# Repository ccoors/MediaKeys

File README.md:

# MediaKeys

| 1  | 2 |
| ------------- | ------------- |
| Play/Pause | Stop  |
| Previous | Next |
| Volume - | Volume + |

The Arduino sketch requires the [Arduino HID Project](https://github.com/NicoHood/HID) (installable from the Arduino IDE)

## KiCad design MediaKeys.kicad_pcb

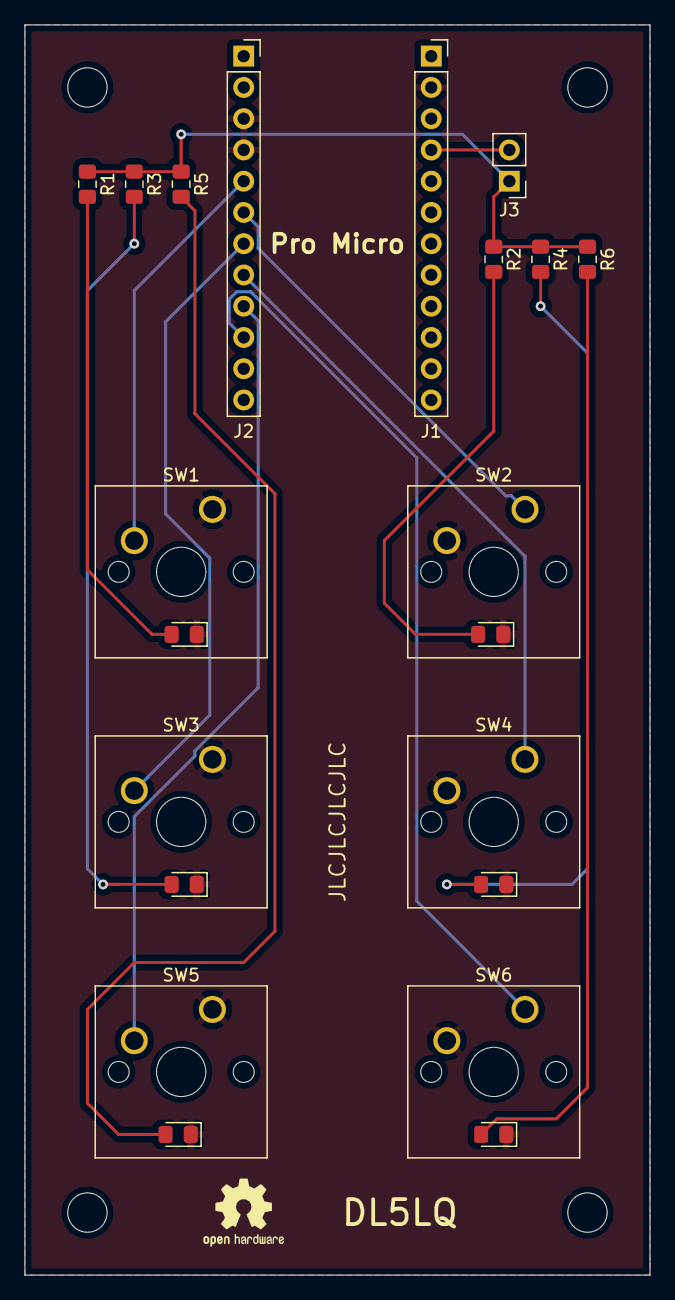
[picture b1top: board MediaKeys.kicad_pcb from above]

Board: 2 copper layers, 50.8 x 101.6 mm, 25 parts (0 on the bottom side), 15 nets.

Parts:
D1, D2, D3, D4, D5, D6: LED; LED_0805_2012Metric_Pad1.15x1.40mm_HandSolder
H1, H2, H3, H4: MountingHole; MountingHole_3.2mm_M3
J1, J2: Conn_01x12_Female; PinSocket_1x12_P2.54mm_Vertical
J3: Conn_01x02_Male; PinHeader_1x02_P2.54mm_Vertical
R1, R2, R3, R4, R5, R6: 1k; R_0805_2012Metric_Pad1.15x1.40mm_HandSolder
SW1, SW2, SW3, SW4, SW5, SW6: SW_Push; SW_Cherry_MX_1.25u_PCB

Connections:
/2: J2.5, SW1.2
/3: J2.6, SW2.1
/4: J2.7, SW3.2
/5: J2.8, SW4.1
/6: J2.9, SW5.2
/7: J2.10, SW6.1
/LEDVCC: J3.1, R1.1, R2.1, R3.1, R4.1, R5.1, R6.1
GND: D1.1, D2.1, D3.1, D4.1, D5.1, D6.1, J1.2, J2.3, J2.4, SW1.1, SW2.2, SW3.1, SW4.2, SW5.1, SW6.2
unnamed: D1.2, R1.2
unnamed: D2.2, R2.2
unnamed: D3.2, R3.2
unnamed: D4.2, R4.2
unnamed: D5.2, R5.2
unnamed: D6.2, R6.2
VCC: J1.4, J3.2

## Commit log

2019-11-17 Add Arduino sketch
2024-05-20 fix: do not spam key release events
